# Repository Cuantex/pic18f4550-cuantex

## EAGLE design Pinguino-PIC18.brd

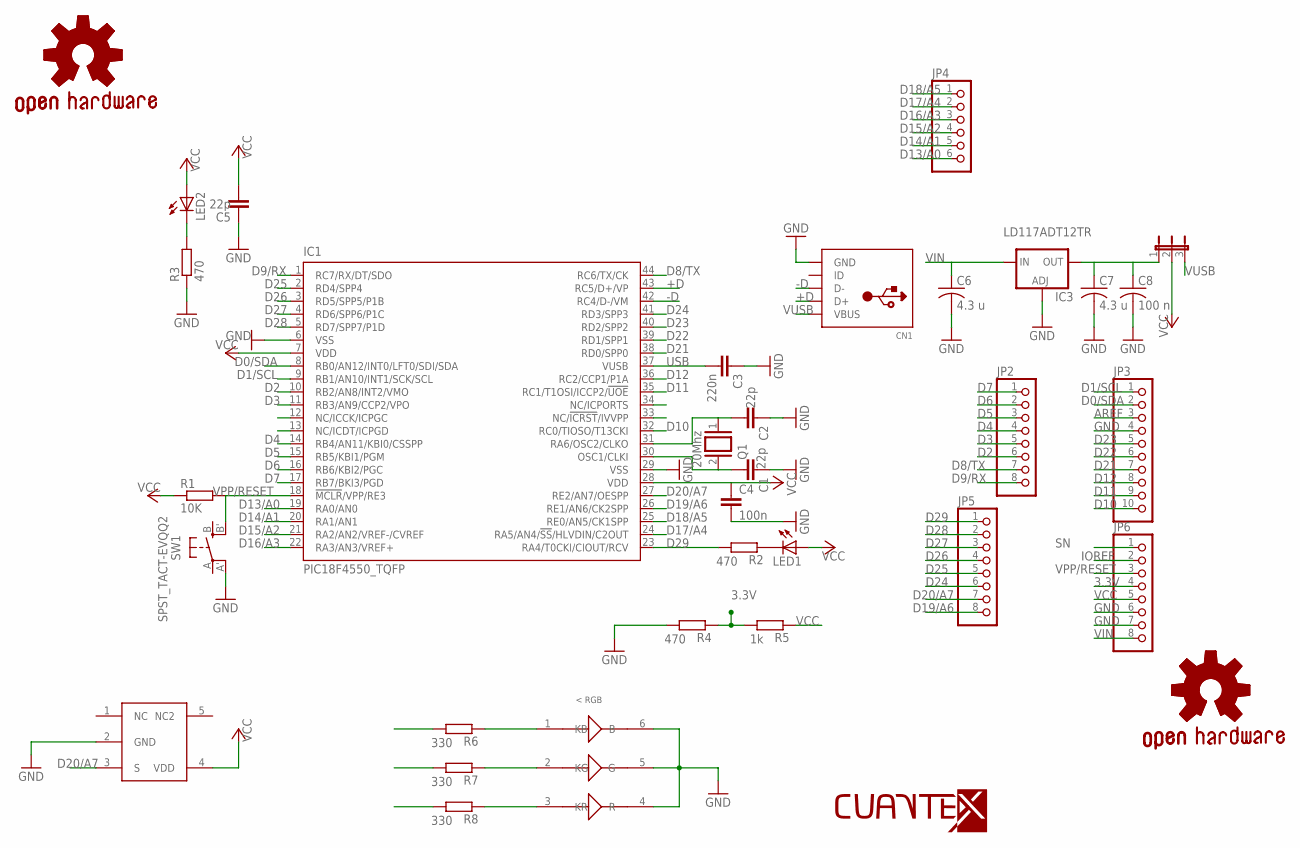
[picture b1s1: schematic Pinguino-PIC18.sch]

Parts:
C1, C2, C5: 22p; C0603
C3: 220n; C0603
C4: 100n; C0603
C6, C7: 4.3 u; C1206K
C8: 100 n; C0603K
CN1: USBMINIB; USB-MINIB
GOLD_ORB_SM1: OSHWLOGO_GOLD_ORB_MED; OSHW1
GOLD_ORB_SM2: OSHWLOGO_GOLD_ORB_SM; OSHW2
IC1: PIC18F4550_TQFP; TQFP44
IC3: LD117ADT12TR; DPACK
JP1: JP2E; JP2
JP2, JP5, JP6: PINHD-1X8; 1X08
JP3: PINHD-1X10; 1X10
JP4: PINHD-1X6; 1X06
LED1, LED2: LED_ESML0603; LED_SML0603
Q1: 20Mhz; QS
R1: 10K; R0603
R2, R3, R4: 470; R0603
R5: 1k; R0603
R6, R7, R8: 330; R0603
SW1: SPST_TACT-EVQQ2; EVQ-Q2
U$1: LOGO-TOP-30MM; C-1
U$3: RGB_SMD; SMD_LED
U$4: SC70

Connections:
3.3V: JP6.4, R4.1, R5.2
+D: CN1.D+, IC1.43 (RC5/D+/VP)
-D: CN1.D-, IC1.42 (RC4/D-/VM)
AREF: JP3.3
D0/SDA: IC1.8 (RB0/AN12/INT0/LFT0/SDI/SDA), JP3.2
D1/SCL: IC1.9 (RB1/AN10/INT1/SCK/SCL), JP3.1
D2: IC1.10 (RB2/AN8/INT2/VMO), JP2.6
D3: IC1.11 (RB3/AN9/CCP2/VPO), JP2.5, R6.2
D4: IC1.14 (RB4/AN11/KBI0/CSSPP), JP2.4
D5: IC1.15 (RB5/KBI1/PGM), JP2.3
D6: IC1.16 (RB6/KBI2/PGC), JP2.2
D7: IC1.17 (RB7/BKI3/PGD), JP2.1
D8/TX: IC1.44 (RC6/TX/CK), JP2.7
D9/RX: IC1.1 (RC7/RX/DT/SDO), JP2.8
D10: IC1.32 (RC0/TIOSO/T13CKI), JP3.10
D11: IC1.35 (RC1/T1OSI/ICCP2/!UOE), JP3.9
D12: IC1.36 (RC2/CCP1/P1A), JP3.8, R7.2
D13/A0: IC1.19 (RA0/AN0), JP4.6
D14/A1: IC1.20 (RA1/AN1), JP4.5
D15/A2: IC1.21 (RA2/AN2/VREF-/CVREF), JP4.4
D16/A3: IC1.22 (RA3/AN3/VREF+), JP4.3
D17/A4: IC1.24 (RA5/AN4/!SS!/HLVDIN/C2OUT), JP4.2
D18/A5: IC1.25 (RE0/AN5/CK1SPP), JP4.1
D19/A6: IC1.26 (RE1/AN6/CK2SPP), JP5.8
D20/A7: IC1.27 (RE2/AN7/OESPP), JP5.7, U$4.3 (S)
D21: IC1.38 (RD0/SPP0), JP3.7, R8.2
D22: IC1.39 (RD1/SPP1), JP3.6
D23: IC1.40 (RD2/SPP2), JP3.5
D24: IC1.41 (RD3/SPP3), JP5.6
D25: IC1.2 (RD4/SPP4), JP5.5
D26: IC1.3 (RD5/SPP5/P1B), JP5.4
D27: IC1.4 (RD6/SPP6/P1C), JP5.3
D28: IC1.5 (RD7/SPP7/P1D), JP5.2
D29: IC1.23 (RA4/T0CKI/CIOUT/RCV), JP5.1, R2.2
GND: C1.1, C2.1, C3.1, C4.2, C5.1, C6.2, C7.2, C8.2, CN1.GND, IC1.6 (VSS), IC1.29 (VSS), IC3.1 (ADJ), JP3.4, JP6.6, JP6.7, R3.1, R4.2, SW1.A' (P1), U$3.4 (R), U$3.5 (G), U$3.6 (B), U$4.2 (GND)
IOREF: JP6.2
unnamed: C1.2, IC1.30 (OSC1/CLKI), Q1.2
unnamed: C2.2, IC1.31 (RA6/OSC2/CLKO), Q1.1
unnamed: LED1.C, R2.1
unnamed: LED2.C, R3.2
unnamed: C7.1, C8.1, IC3.4 (OUT), JP1.1
unnamed: R6.1, U$3.1 (KB)
unnamed: R7.1, U$3.2 (KG)
unnamed: R8.1, U$3.3 (KR)
SN: JP6.1
USB: C3.2, IC1.37 (VUSB)
VCC: C4.1, C5.2, IC1.7 (VDD), IC1.28 (VDD), JP1.2, JP6.5, LED1.A, LED2.A, R1.1, R5.1, U$4.4 (VDD)
VIN: C6.1, IC3.3 (IN), JP6.8
VPP/RESET: IC1.18 (!MCLR!/VPP/RE3), JP6.3, R1.2, SW1.B' (S1)
VUSB: CN1.VBUS, JP1.3

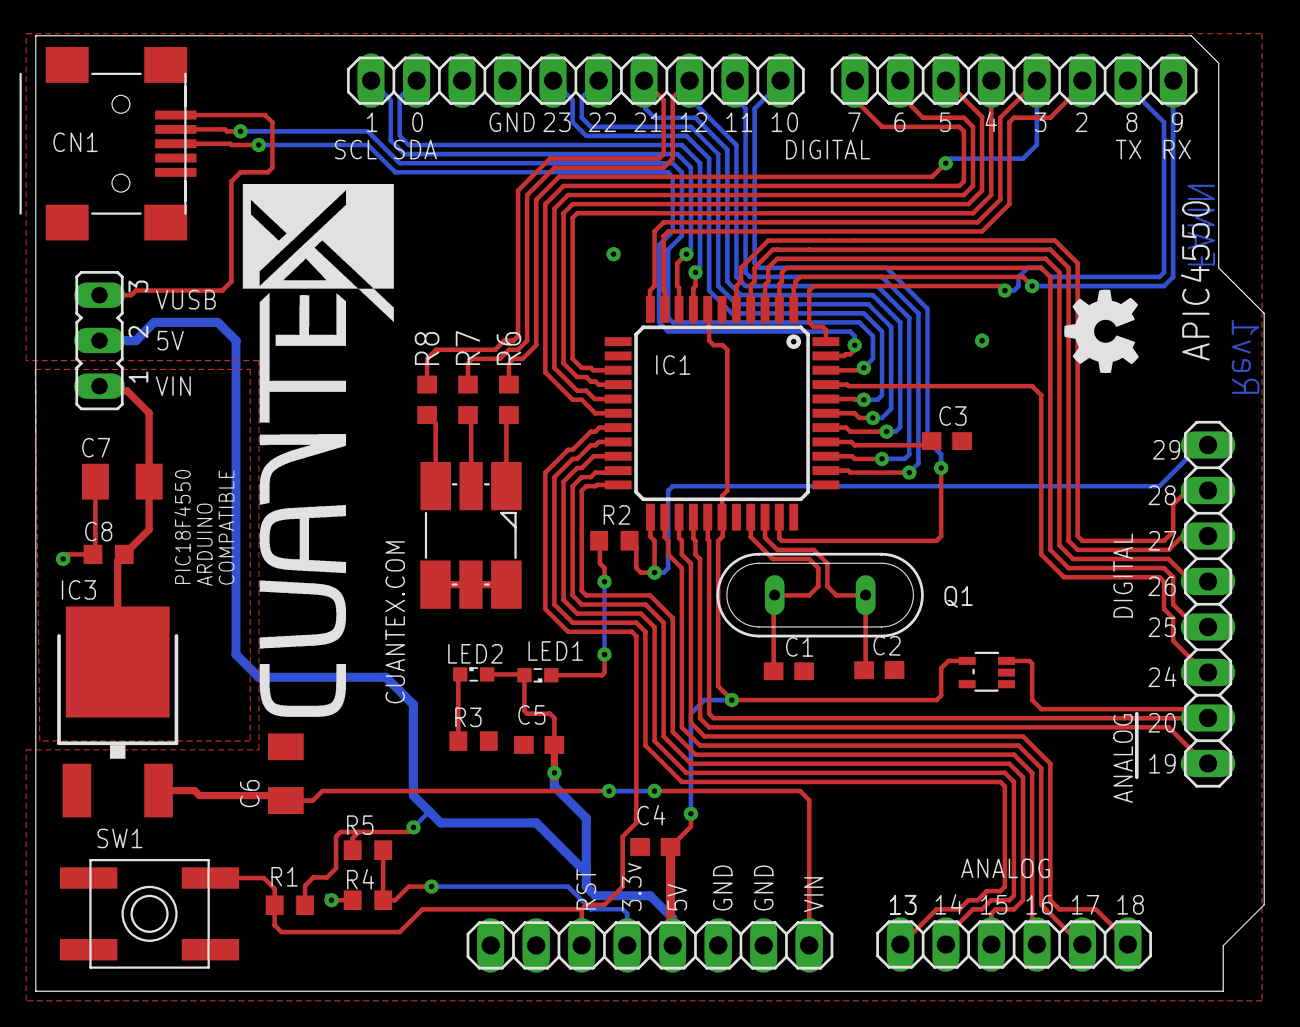
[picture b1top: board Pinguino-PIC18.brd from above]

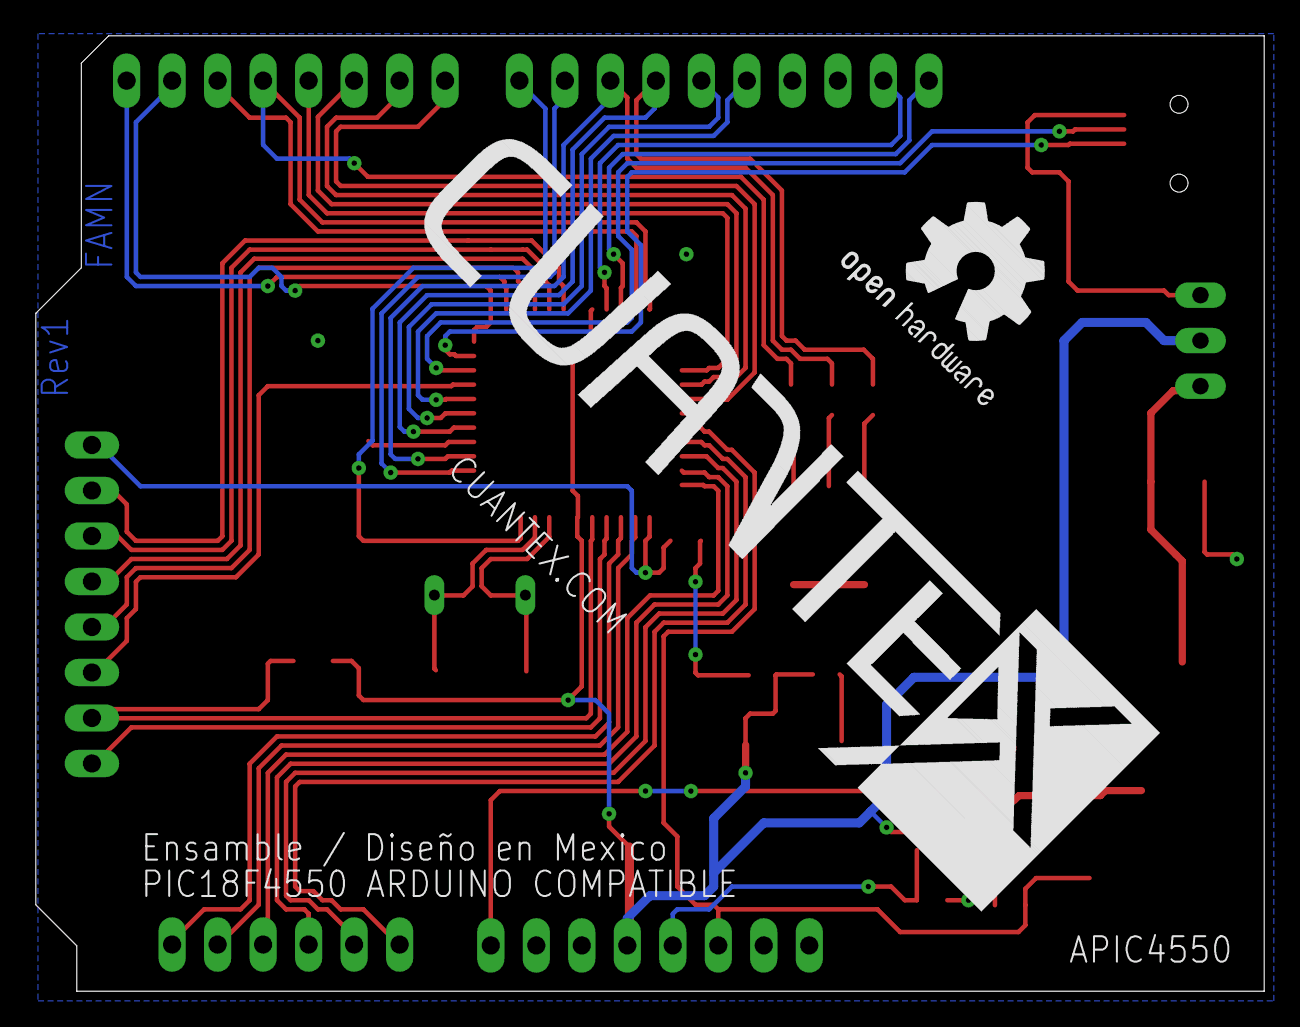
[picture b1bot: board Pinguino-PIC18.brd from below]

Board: 2 copper layers, 68.6 x 53.3 mm, 35 parts (2 on the bottom side), 47 nets.

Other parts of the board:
U$2: LOGO-TOP-40MM; C-3

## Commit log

2016-03-28 Archivos en git
